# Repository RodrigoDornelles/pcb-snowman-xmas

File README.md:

> printed circuit board artistic badge with xmas theme for [@Juliallabs](https://github.com/juliallabs) (JuliaLabs) competition (2020/NOVEMBER) promoved by [PCBWAY](https://pcbway.com)

## About ##
Musical snowman badge where all the electrical components are useful for decoration design, this PCB will play a complete Christmas music sound (melody and harmony) because of its 4 buzzers and it will also have a led pulse in a rhythmic way, as the hat rotates (knob pot) will increase the volume or turn off the badge.

* [click here to view all images](https://github.com/RodrigoDornelles/pcb-snowman-xmas/blob/master/IMAGES.md)

## Requirements ##
| Dependency | Platform | Description |
| :--------- | -------- | :---------- |
| [RodrigoDornelles/arduino-tone-pitch](https://github.com/RodrigoDornelles/arduino-tone-pitch) | arduino lib | improve the pitch tune of piezos |
| [RodrigoDornelles/arduino-soft-buzzer](https://github.com/RodrigoDornelles/arduino-soft-buzzer) | arduino lib | allow multiple piezos to be played simultaneously |
| [SnapEDA CMT-8530S-SMT-TR](https://www.snapeda.com/parts/CMT-8530S-SMT-TR/CUI%20Devices/view-part/649163/) | eagle lib | fotoprint and symbol to **Eagle** project |
| [SnapEDA ATTINY85-20PU](https://www.snapeda.com/parts/ATTINY85-20PU/Microchip/view-part/?ref=search&t=attiny85) | autodesk 3d | fotoprint and symbol to **Eagle** project |
| [SnapEDA ATTINY85-20PU](https://www.snapeda.com/parts/ATTINY85-20PU/Microchip/view-part/?ref=search&t=attiny85) | autodesk 3d | added in the **Eagle** project for 3D view in the  **Fusion 360** |
| [GrabCad LED 3mm 2](https://grabcad.com/library/led-3mm-2) | autodesk 3d | added in the **Eagle** project for 3D view in the  **Fusion 360** |
| [GrabCad Potentiometer 3](https://grabcad.com/library/potentiometer-3) | autodesk 3d | added in the **Eagle** project for 3D view in the  **Fusion 360** |
| [CUI Devices CMT-8530S-SMT-TR](https://www.cuidevices.com/product/resource/3dmodel/cmt-8530s-smt-tr) | autodesk 3d | added in the **Eagle** project for 3D view in the  **Fusion 360** |

## First Draft ##
|  |- 2x Led's<br/><br/>- 1x Potentiometer<br/><br/>- 3x Buzzer's for musical harmony<br/><br/>- 1x Buzzer for musical melody<br/><br/>_How work: when you turn your nose (potentiometer) you will start playing a Christmas song the more you turn the louder you will play._ |
| - | :- |

## Bill of Materials ##
| # | Designator | Qty | Part Number | Description |
| - | :--------- | --- | :---------- | :---------- | 
| 1 | R1 | 1 | WH148-1 10K L20 | RES POT 10.0K OHM 0.25W PTH |
| 2 | R2,R3,R4,R5,R6,R7 | 6 | RND1550805S8F2400T5E | RES 110.0 OHM 0.125W 1% 0815 SMD |
| 3 | LS1,LS2,LS3,LS4 | 4 | CMT-8530S-SMT-TR | 8.5 mm Magnetic Audio Transducer Passive Buzzer SMT  |
| 4 | U1 | 1 | ATTINY85-20PU | 8bit AVR Microcontroller Programmable Flash PTH |
| 5 | LED1 | 1 | L-424HDT | 2.25 V Red LED 3mm Cylindrical |
| 6 | ???| ? | | Battery Holder |
| 7 | D1,D2,D3,D4 | 4 | SMA-DO214AC | Diode SMD |

## Eletronic Circuit ##

## 3D View ##
|  | 
| - |

|  | |
| - | - |

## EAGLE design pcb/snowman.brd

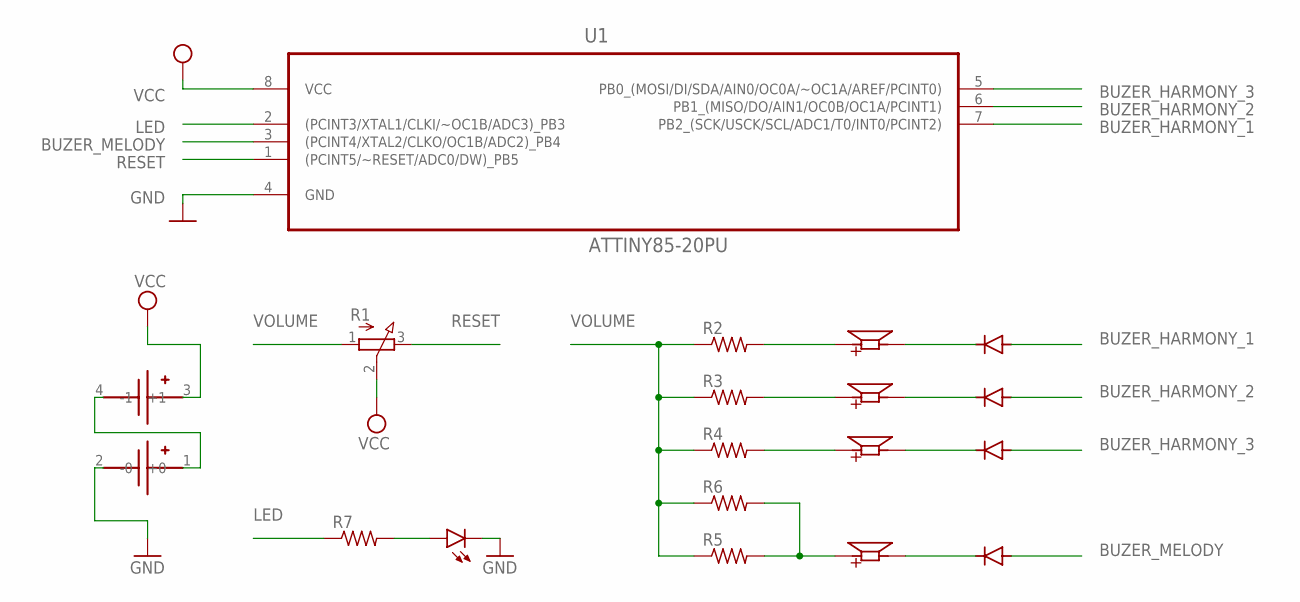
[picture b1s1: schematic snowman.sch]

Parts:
D1, D2, D3, D4: GF1; SMA-DO214AC
LED1: LED3MM
LS1, LS2, LS3, LS4: CMT-8530S-SMT; CUI_CMT-8530S-SMT
R1: 3RP/1610N
R2, R3, R4, R5, R6, R7: R-US_R0805; R0805
U1: ATTINY85-20PU; DIP254P762X533-8
U$1: BLOSSOM-BLM-18650-2PCS

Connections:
BUZER_HARMONY_1: D4.A, U1.7 (PB2_(SCK/USCK/SCL/ADC1/T0/INT0/PCINT2))
BUZER_HARMONY_2: D3.A, U1.6 (PB1_(MISO/DO/AIN1/OC0B/OC1A/PCINT1))
BUZER_HARMONY_3: D2.A, U1.5 (PB0_(MOSI/DI/SDA/AIN0/OC0A/~OC1A/AREF/P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)
BUZER_MELODY: D1.A, U1.3 ((PCINT4/XTAL2/CLKO/OC1B/ADC2)_PB4)
GND: LED1.K (C), U1.4 (GND), U$1.2 (-0)
LED: R7.1, U1.2 ((PCINT3/XTAL1/CLKI/~OC1B/ADC3)_PB3)
unnamed: LS4.P, R3.2
unnamed: LS2.P, R2.2
unnamed: LS3.P, R4.2
unnamed: LED1.A, R7.2
unnamed: LS1.P, R5.2, R6.2
unnamed: D4.K (C), LS2.N
unnamed: D3.K (C), LS4.N
unnamed: D2.K (C), LS3.N
unnamed: D1.K (C), LS1.N
unnamed: U$1.1 (+0), U$1.4 (-1)
RESET: R1.3 (E), U1.1 ((PCINT5/~RESET/ADC0/DW)_PB5)
VCC: R1.2 (S), U1.8 (VCC), U$1.3 (+1)
VOLUME: R1.1 (A), R2.1, R3.1, R4.1, R5.1, R6.1

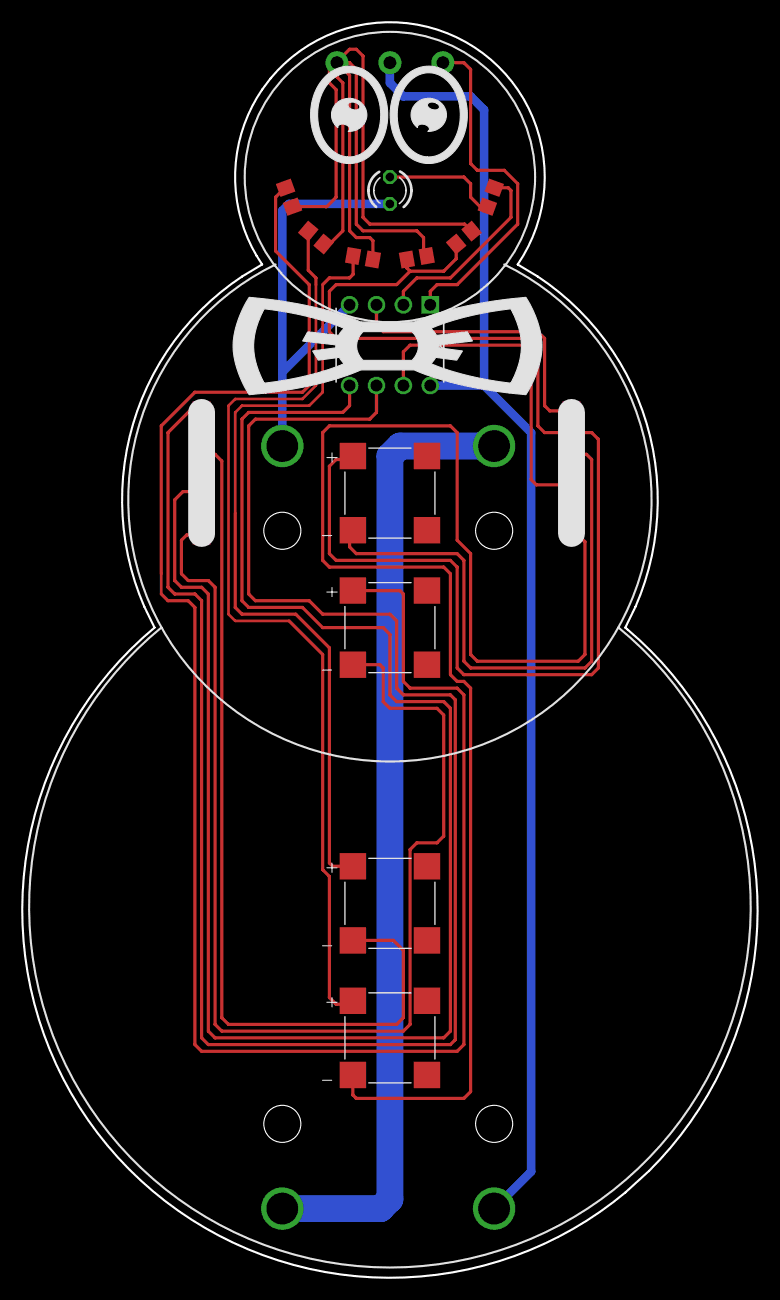
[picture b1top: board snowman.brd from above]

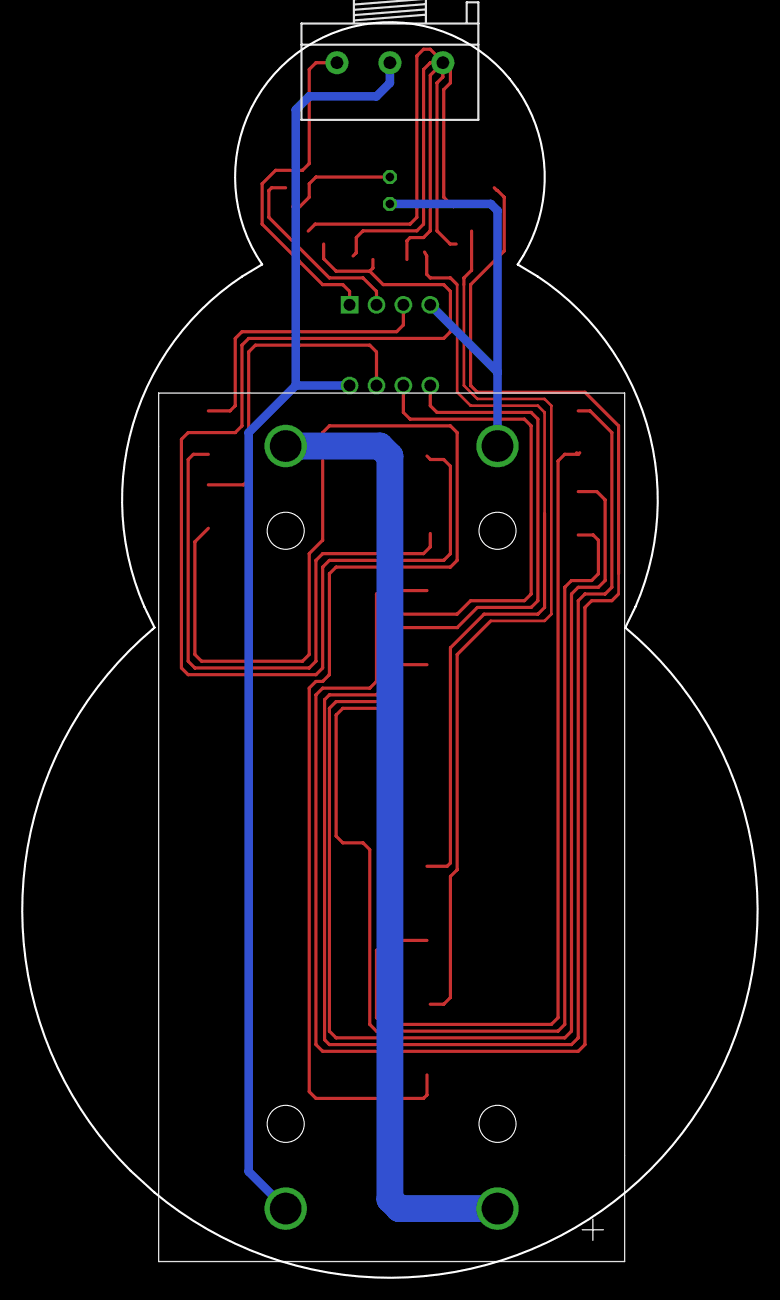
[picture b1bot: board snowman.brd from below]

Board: 2 copper layers, 69.4 x 118.5 mm, 18 parts (2 on the bottom side), 19 nets.

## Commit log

2020-11-06 improve logical circuit
2020-11-06 draft board
2020-11-06 smyle?
2020-11-06 order components && init pcb trail
2020-11-07 add power circuit
2020-11-07 pcb improve layout
2020-11-07 pcb add art bowtie
2020-11-07 add pcb outline
2020-11-07 center piezos (clothing button)
2020-11-08 updates made in livestream
2020-11-08 change eletronic circuit image
2020-11-08 add 3d
2020-11-09 upload 3d images
2020-11-09 renamed: images/snow3front.png -> images/snow3dfront.png
2020-11-09 change pcb colors
2020-11-18 add dependencies to README.md
2020-11-18 add Bill of Materials header to docs
2020-11-18 update bill of materials
2020-11-18 add PTH types in bill of materials
2020-11-18 change Buzzer type smd to smt
2020-11-20 add diode current filter to buzzers
2020-11-20 update copper trails
2020-11-20 adjust arms
2020-11-23 simplify bill of materials
2020-11-23 add about to README
2020-11-23 add shields to README
2020-11-23 update images
2020-11-23 add link to view images
2020-11-25 add resistor & potentiometer & led part numbers
2020-11-25 replace component CR-AA -> BLOSSOM-BLM-18650-2PCS
2020-11-25 update bom list part numbers
